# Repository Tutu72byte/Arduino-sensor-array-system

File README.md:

# Arduino sensor array - Hardware and Software developement

## General Description

This project is a full Hardware and Software implementation of a sensor array built for automated security purposes. The hardware (Schematic and PCB layout) was designed using **KiCad 9.0** and the code was written in **C++** and uploaded via the **platformio** extension for VSCode

With this project's prototype I managed to win the 3rd place at the **FutureShapers Hackathon 2026**, organized by **Honeywell, Politehnica Bucharest, EELISA and Groupe INSA** (Photos and Video attached). It was presented under the name "ASG: Automated Security Guardian"

---

## Architecture & Functional Blocks

1. **Central Processing Unit (Arduino UNO):**
   * Dedicated microcontroller for embedded applications.
   * Integrated high-speed communication protocols such as **I2C** for this project
   * Easily compatible with different programming devices using a USB interface

2. **Input sensors**
   * ambient temperature (DHT11)
   * ambient light sensor (Photoresistor CDS-55) working in a voltage divider configuration
   * ultrasound distance sensor (HC-SR501 Set to a 20cm threshold)
   * button simulating a fire/general emergency alarm and also a shutdown mechanism.

3. **Outputs and interface**
   * MAIN OUTPUT: 2x16 **LCD display**
   * 3 leds: Red for proximity breach and alarm, yellow and green for temperature status
   * Passive Buzzer alarm

4. **Power Management:**
   * The photoresistor acts as a light detector and is programmed to **turn off the backlight** of the LCD if low ambient light is detected

---

## PCB Layout & Design Guidelines
The printed circuit board (PCB) was routed following standard practices such as:

* **2-Layer Stackup Strategy:**
  * **Layer 1a (Top):** Primary component placement, high-speed signals and larger power traces
  * **Layer 1b (Ground Plane):** A solid, continuous ground plane (`GND`) ensuring a low-impedance return path for high-speed signals and effective electromagnetic shielding (EMI).
  * **Layer 4 (Bottom):** Secondary routing layer.

* **Component Placement:** 
  * The length of all copper paths was tuned to ensure minimum impedance (For power traces) and overall cost effectiveness.

---

## Technical Specifications

* **Power Input:** stable +5V via the Arduino's integrated voltage regulator
* **Connectivity & Interfaces:** 
  * I2C communication protocol for the LCD output display
  * Fine control of the servo motor (Which moves the ultrasound sensor to cover ~170deg FOV) via PWM
* **Status Indication:** 3 status LEDs (`LED1 - RED`, `LED2 - YELLOW`, `LED3 - GREEN`).
* **JSON compatibility** for **serial data transfer** between the device and a web server allowing **long distance monitoring** of the system

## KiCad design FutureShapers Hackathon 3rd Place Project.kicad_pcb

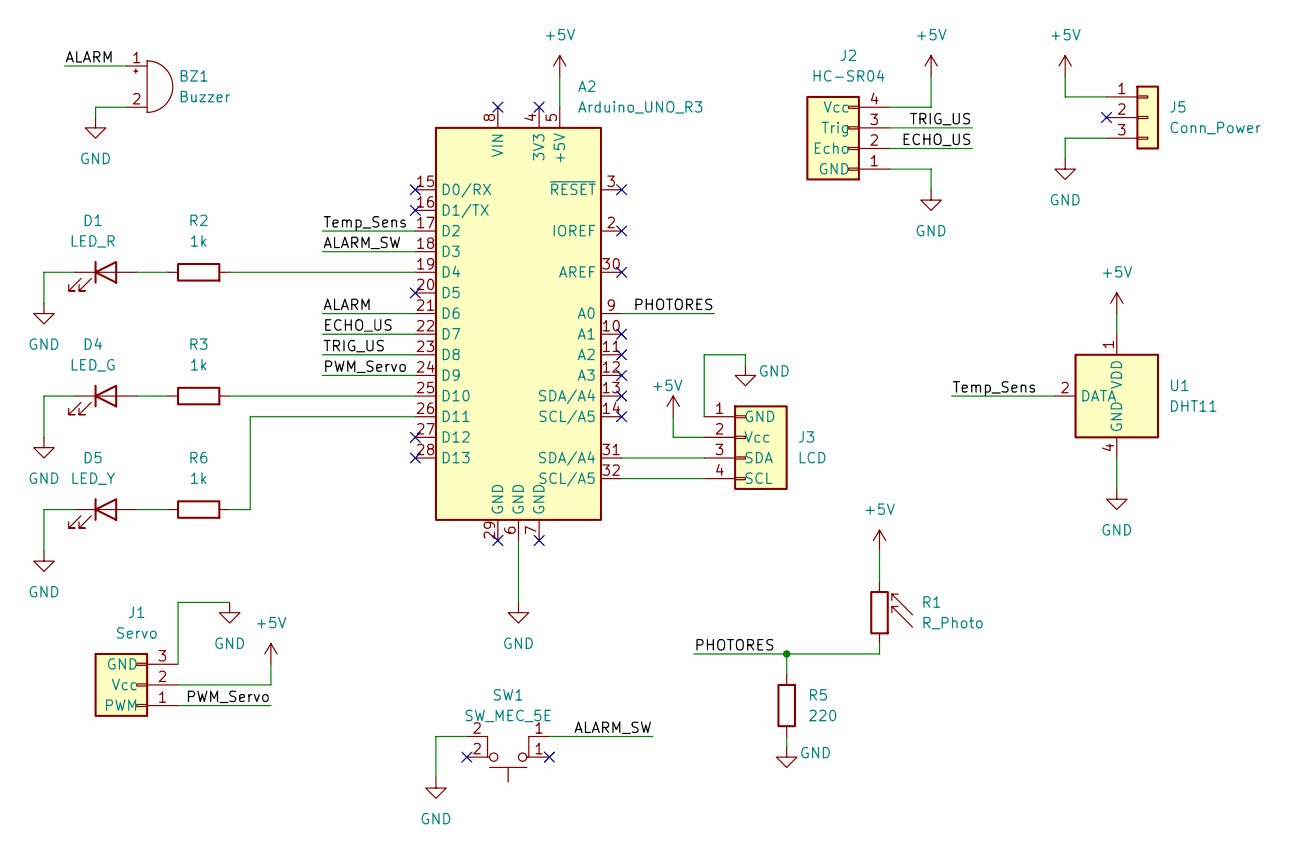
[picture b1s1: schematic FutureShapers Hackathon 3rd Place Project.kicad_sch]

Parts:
A2: Arduino_UNO_R3
BZ1: Buzzer; PinHeader_1x02_P1.00mm_Vertical_SMD_Pin1Left
D1: LED_R; LED_0402_1005Metric
D4: LED_G; LED_0402_1005Metric
D5: LED_Y; LED_0402_1005Metric
J1: Servo; Banana_Jack_3Pin
J2: HC-SR04; PinHeader_2x02_P1.00mm_Vertical_SMD
J3: LCD; PinHeader_2x02_P1.00mm_Vertical_SMD
J5: Conn_Power; BarrelJack_Horizontal
R1: R_Photo; R_LDR_5.1x4.3mm_P3.4mm_Vertical
R2, R3, R6: 1k; R_0603_1608Metric_Pad0.98x0.95mm_HandSolder
R5: 220; R_0402_1005Metric_Pad0.72x0.64mm_HandSolder
SW1: SW_MEC_5E; SW_PUSH_6mm
U1: DHT11; Aosong_DHT11_5.5x12.0_P2.54mm

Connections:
+5V: A2.5 (+5V), J1.2 (Vcc), J2.4 (Vcc), J3.2 (Vcc), J5.1, R1.2, U1.1 (VDD)
/ALARM: A2.21 (D6), BZ1.1 (+)
/ALARM_SW: A2.18 (D3), SW1.1
/ECHO_US: A2.22 (D7), J2.2 (Echo)
/PHOTORES: A2.9 (A0), R1.1, R5.2
/PWM_Servo: A2.24 (D9), J1.1 (PWM)
/TRIG_US: A2.23 (D8), J2.3 (Trig)
/Temp_Sens: A2.17 (D2), U1.2 (DATA)
GND: A2.6 (GND), BZ1.2 (-), D1.1 (K), D4.1 (K), D5.1 (K), J1.3 (GND), J2.1 (GND), J3.1 (GND), J5.3, R5.1, SW1.2, U1.4 (GND)
unnamed: A2.19 (D4), R2.2
unnamed: A2.25 (D10), R3.2
unnamed: A2.26 (D11), R6.2
unnamed: D1.2 (A), R2.1
unnamed: D4.2 (A), R3.1
unnamed: D5.2 (A), R6.1
unnamed: A2.32 (SCL/A5), J3.4 (SCL)
unnamed: A2.31 (SDA/A4), J3.3 (SDA)

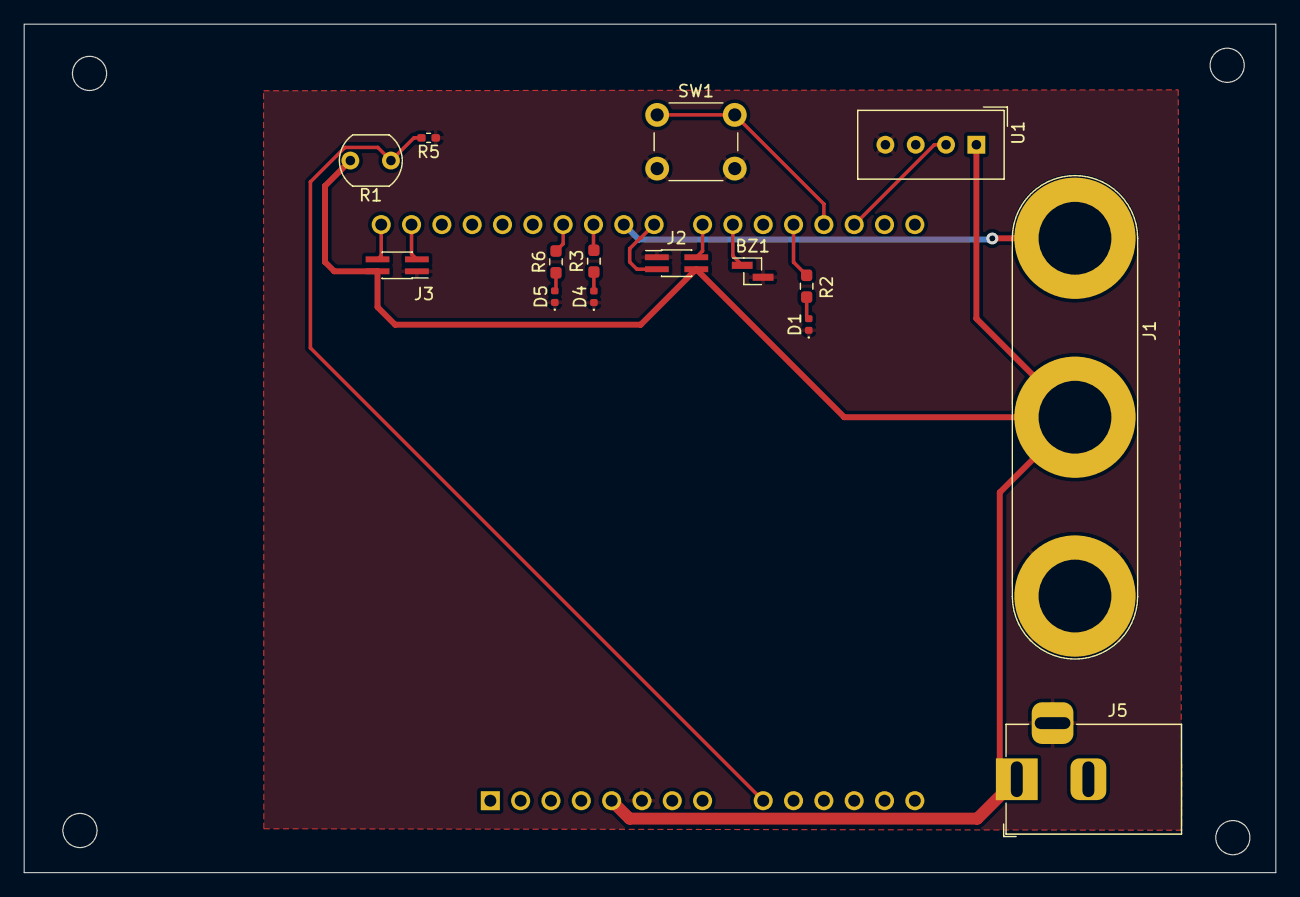
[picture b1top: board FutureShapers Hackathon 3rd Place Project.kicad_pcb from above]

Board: 2 copper layers, 104.9 x 71.1 mm, 16 parts (1 on the bottom side), 17 nets.
